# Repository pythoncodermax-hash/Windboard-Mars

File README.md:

# Windboard-Mars
Here is my custom Hackpad for windows shortcuts

This is my first time working with Ki Cad but overall i found it good.

It is a 9 button keyboard with macros assigned to each key and also an oled which will display some moving pixels.

The macros on the buttons are:

1. Alt F4
2. Quick Link, Win + X
3. Opens Chrome
4. Win + D, minimises applications
5. Undo delete Tab
6. Open Github
7. Open VS Code
8. Lock Screen
9. Opens Steam

For the oled so far i have just made some dots which slowly disapear out of frame until their is none.

Experience:

I had never used Ki cad before making a Hackpad but i found it easy to use after watching a video and following the turorial.
Fusion 360 was a bigger challenge as i had to remake the case a few times to adjust dimensions but because i had some previous experience it was fun to do. I used KMK for the firmware and i found it pretty straight forward to use however i will have to test it out once i build the board as i am unsure how to test it. I will update this repository once i am finished building the physical Windboard.

Overall i like the project and i can definitely see it being useful in future projects such as potentially building a fully custom keyboard as my current one is getting old.

Navigating the Repository:
The Cad, Firmware and PCB folder are just overviews of the project and are ways to view what it looks like.
The production folder contains everything that needs to be 3D printed, Manufactured and the firmware which is the same as in the Firmware folder.

Tip:
When making the PCB watch the video linked to the Hackpad tutorial on Matrix wiring, it is really good and showed me how to do it.

Latest Update:
I have decided to switch to QMK as it has better documentation for OLEDS. So today i switched all my code from KMK to QMK and it honestly wasnt that bad. I will not that when i first tried on mac i found it hard to install but windows seemed like a better option. The documentation is good but i will also shoutout 
theseagulldevs as he had a similar setup to me and looking at his code as well as the documentation helped me understand how the whole thing worked. Hopefully the code works now so we will see when the Windboard is assembled.

Here is the CAD design made in Fusion 360 to show what the Windboard would look like.

Here is a side on view.

Here is the PCB i designed showing the back.

Here is the front of the PCB where the key switches and oled screen will go.

Here is the PCB design.

This is the schematic that was used to design the PCB.

This is the full design in fusion 360 with the colour blue for the case as that is the colour it will be 3D printed.

<h1> Bill Of Materials: </h1>
<ol>
  
<li>9x Cherry MX switches </li>
<li>9x DSA keycaps</li> 
<li>1x 0.91" 128x32 OLED Display</li>
<li>9x 1N4148 DO-35 Diodes</li>
<li>XIAO RP2040</li>
<li>1x case (2 3d printed parts</li> 
<li>4x M3x16mm SHCS Bolts</li>
<li>4x M3x5x4 Heatset inserts</li>
</ol>

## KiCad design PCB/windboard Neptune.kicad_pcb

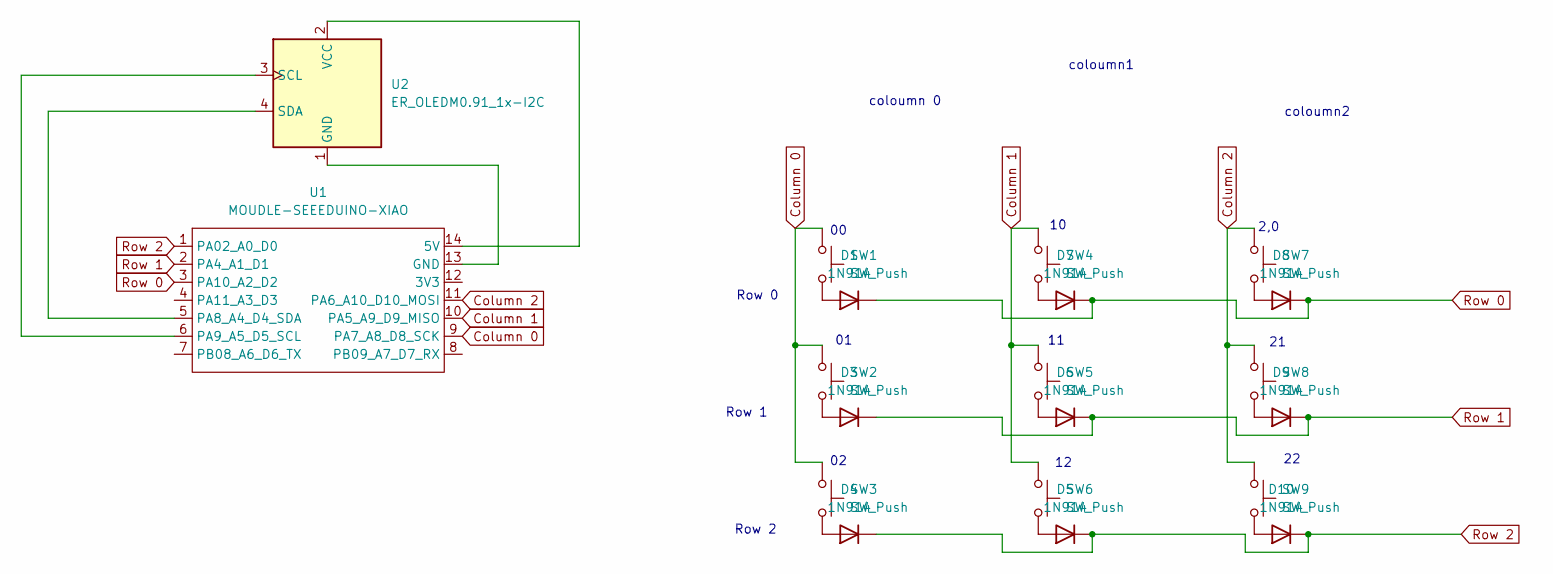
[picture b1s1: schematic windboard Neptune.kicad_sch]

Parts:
D1, D3, D4, D5, D6, D7, D8, D9, D10: 1N914; D_DO-35_SOD27_P7.62mm_Horizontal
SW1, SW2, SW3, SW4, SW5, SW6, SW7, SW8, SW9: SW_Push; SW_Cherry_MX_1.00u_PCB
U1: MOUDLE-SEEEDUINO-XIAO; XIAO-Generic-Hybrid-14P-2.54-21X17.8MM
U2: ER_OLEDM0.91_1x-I2C

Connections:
Column 0: SW1.1, SW2.1, SW3.1, U1.9 (PA7_A8_D8_SCK)
Column 1: SW4.1, SW5.1, SW6.1, U1.10 (PA5_A9_D9_MISO)
Column 2: SW7.1, SW8.1, SW9.1, U1.11 (PA6_A10_D10_MOSI)
unnamed: D1.2 (A), SW1.2
unnamed: D3.2 (A), SW2.2
unnamed: D4.2 (A), SW3.2
unnamed: D5.2 (A), SW6.2
unnamed: D6.2 (A), SW5.2
unnamed: D7.2 (A), SW4.2
unnamed: D8.2 (A), SW7.2
unnamed: D9.2 (A), SW8.2
unnamed: D10.2 (A), SW9.2
unnamed: U1.14 (5V), U2.2 (VCC)
unnamed: U1.13 (GND), U2.1 (GND)
unnamed: U1.5 (PA8_A4_D4_SDA), U2.4 (SDA)
unnamed: U1.6 (PA9_A5_D5_SCL), U2.3 (SCL)
Row 0: D1.1 (K), D7.1 (K), D8.1 (K), U1.3 (PA10_A2_D2)
Row 1: D3.1 (K), D6.1 (K), D9.1 (K), U1.2 (PA4_A1_D1)
Row 2: D4.1 (K), D5.1 (K), D10.1 (K), U1.1 (PA02_A0_D0)

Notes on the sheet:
Row 0
coloumn1
Row 2
coloumn 0
2,0
Row 1
coloumn2

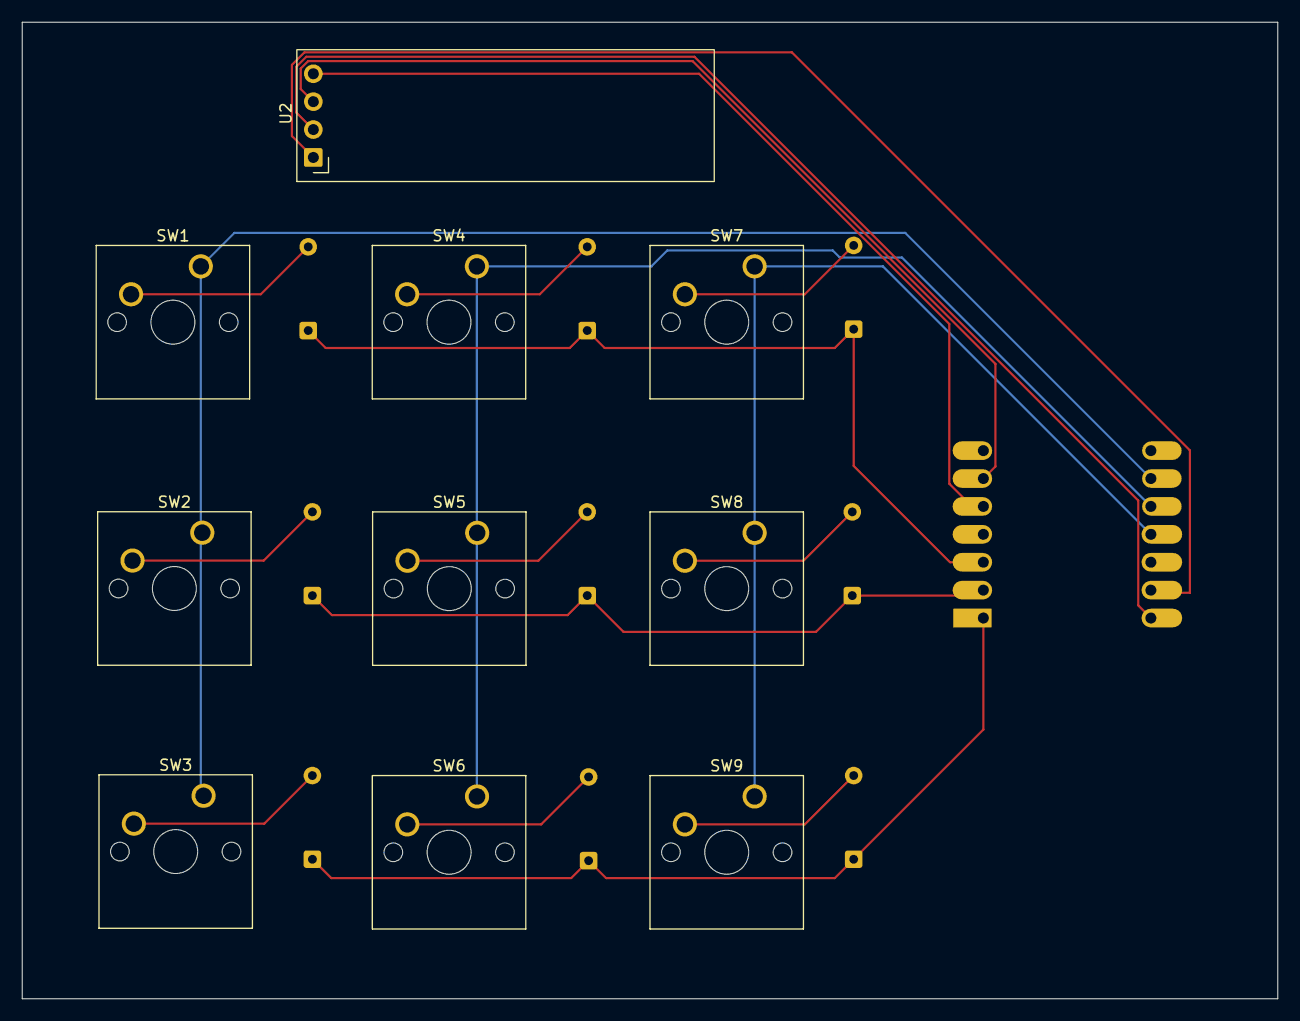
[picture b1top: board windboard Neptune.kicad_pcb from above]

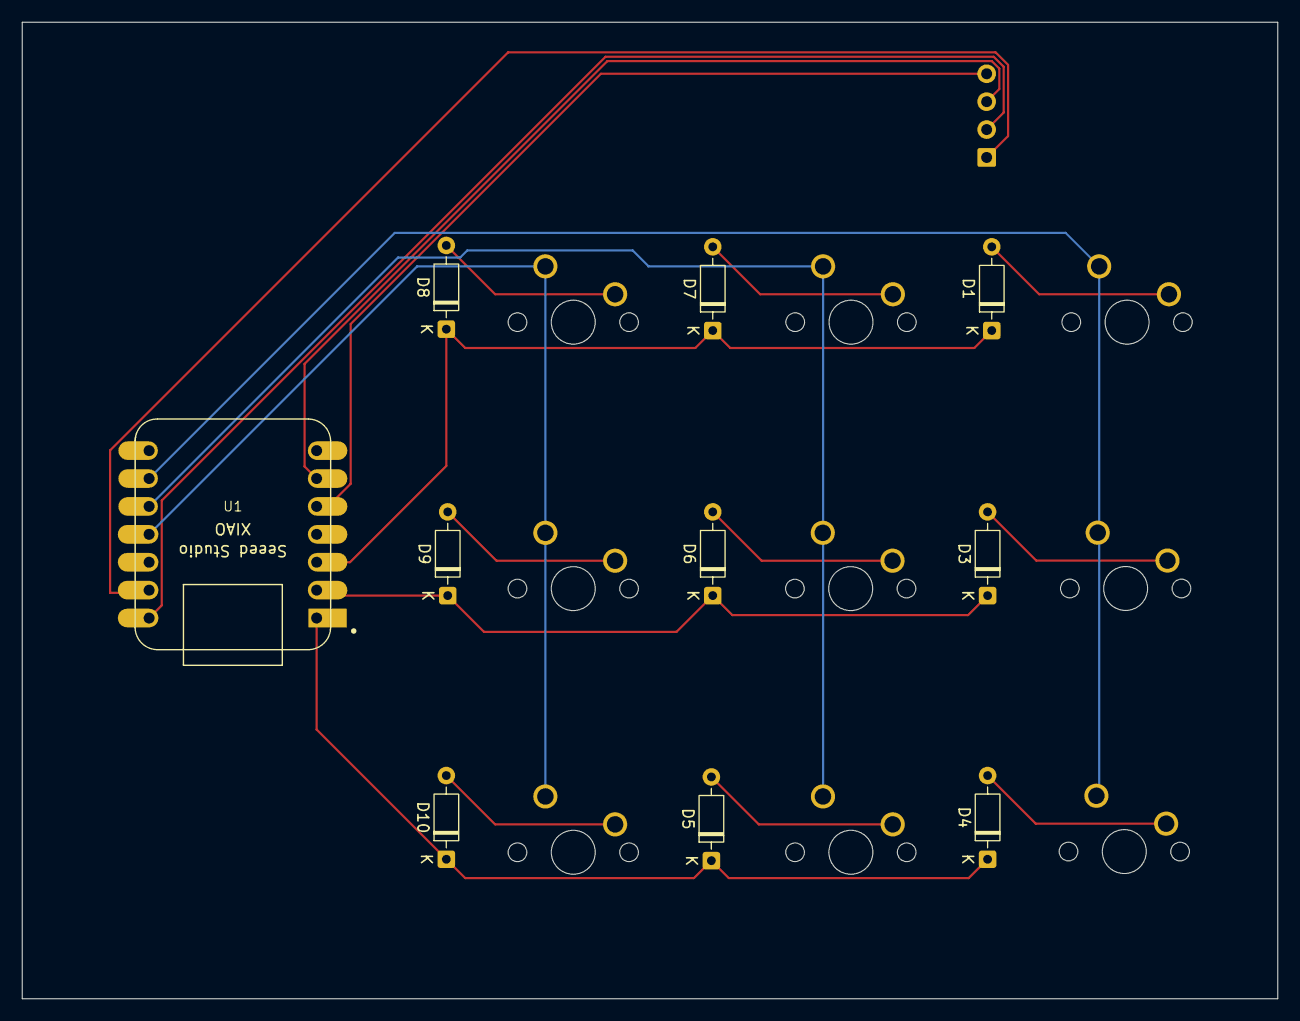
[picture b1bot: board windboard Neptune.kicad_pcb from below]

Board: 2 copper layers, 114.3 x 88.9 mm, 20 parts (10 on the bottom side), 19 nets.

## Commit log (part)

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2026-06-20 Rename main copy.py to Firmware/main copy.py
2026-06-20 Rename windboard Neptune.kicad_pcb to PCB/windboard Neptune.kicad_pcb
2026-06-20 Rename windboard Neptune.kicad_pro to PCB/windboard Neptune.kicad_pro
2026-06-20 Rename windboard Neptune.kicad_sch to PCB/windboard Neptune.kicad_sch
2026-06-20 Rename ~windboard Neptune.kicad_pcb.lck to PCB/~windboard Neptune.kicad_pcb.lck
2026-06-20 Rename ~windboard Neptune.kicad_pro.lck to PCB/~windboard Neptune.kicad_pro.lck
2026-06-20 Add files via upload
    Just a placeholder as my laptop crashes when i try and download the complete .STEP files.
2026-06-20 Rename keyboard case.step to CAD/keyboard case.step
2026-06-20 Create Description
2026-06-20 Create Overview
2026-06-20 Create Firmware
2026-06-22 Update Description
2026-06-22 Create QMK
2026-06-22 Rename Firmware/config.h to Firmware/QMK/config.h
2026-06-22 Rename Firmware/keyboard.json to Firmware/QMK/keyboard.json
2026-06-22 Rename Firmware/keymap.c to Firmware/QMK/keymap.c
2026-06-22 Rename Firmware/readme.md to Firmware/QMK/readme.md
2026-06-22 Rename Firmware/rules.mk to Firmware/QMK/rules.mk
2026-06-22 Rename Firmware/main copy.py to Firmware/KMK/main copy.py
2026-06-23 Update and rename Firmware to Firmware Overview
